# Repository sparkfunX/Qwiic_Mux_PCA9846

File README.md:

SparkFun PCA9846 Qwiic I2C Mux
===========================================================

[*SparkX Qwiic Mux - PCA9846 (SPX-22362)*](https://www.sparkfun.com/products/22362)

Do you have too many sensors with the same I<sup>2</sup>C address? Connect them to the SparkX PCA9846 Qwiic Mux to get them all talking on the same bus! This Qwiic Mux enables communication with multiple I<sup>2</sup>C devices that have the same address. This Qwiic Mux also has eight configurable addresses of its own, allowing for up to 32 I<sup>2</sup>C buses on a single connection. To make it even easier to use this multiplexer, all communication is enacted exclusively via I<sup>2</sup>C, utilizing our handy Qwiic system.

The PCA9846 Qwiic Mux is very similar to our classic [8-channel Qwiic Mux](https://www.sparkfun.com/products/16784), except:

* It has four multiplexed Qwiic ports, plus Qwiic Main In and Out connections, on a super-cute 1" x 1" PCB
* The PCA9846 has a "Who Am I" (Device ID) product identification register which makes it _much_ easier to detect in auto-detect DataLogger / OpenLog applications.

Feel like supporting open source hardware? 
Buy a [board](https://www.sparkfun.com/products/22362) from SparkFun!

Repository Contents
-------------------

* **/Documents** - Datasheet for the PCA9846
* **/Hardware** - Eagle CAD files for the PCB, schematic and dimensions

Arduino Library
--------------

* **[Arduino Library](https://github.com/sparkfun/SparkFun_PCA9846_Mux_Arduino_Library)** - Arduino Library for the PCA9846 I<sup>2</sup>C Mux
* **[Installing an Arduino Library Guide](https://learn.sparkfun.com/tutorials/installing-an-arduino-library)** - Basic information on how to install an Arduino library.

Address Configuration
--------------

The PCA9846 actually supports 16 I<sup>2</sup>C addresses, but to implement all 16 we would have had to include another three solder jumpers.
This is a busy little board, so we decided to only implement 8 configurable addresses.

The PCA9846 appears on two I2C addresses:

* The mux address defined by the A0-A4 jumpers
* Address 0x7C - which is used to read the Device ID

The default mux address is 0x70 (unshifted). You can change it by opening and closing (soldering) the five address jumper pads as follows:

**Jumper Address Selection (Unshifted):**

| Address | A4 | A3 | A2 | A1 | A0 |
|---|---|---|---|---|---|
| 0x70 | Open | Open | Open | Open | **Closed** |
| 0x71 | Open | Open | Open | **Closed** | Open |
| 0x72 | Open | Open | **Closed** | Open | Open |
| 0x73 | Open | **Closed** | Open | Open | Open |
| 0x74 | **Closed** | Open | Open | Open | **Closed** |
| 0x75 | **Closed** | Open | Open | **Closed** | Open |
| 0x76 | **Closed** | Open | **Closed** | Open | Open |
| 0x77 | **Closed** | **Closed** | Open | Open | Open |

License Information
-------------------

This product is _**open source**_! 

Please use, reuse, and modify these files as you see fit. Please maintain attribution to SparkFun Electronics and release anything derivative under the same license.

Distributed as-is; no warranty is given.

- Your friends at SparkFun.

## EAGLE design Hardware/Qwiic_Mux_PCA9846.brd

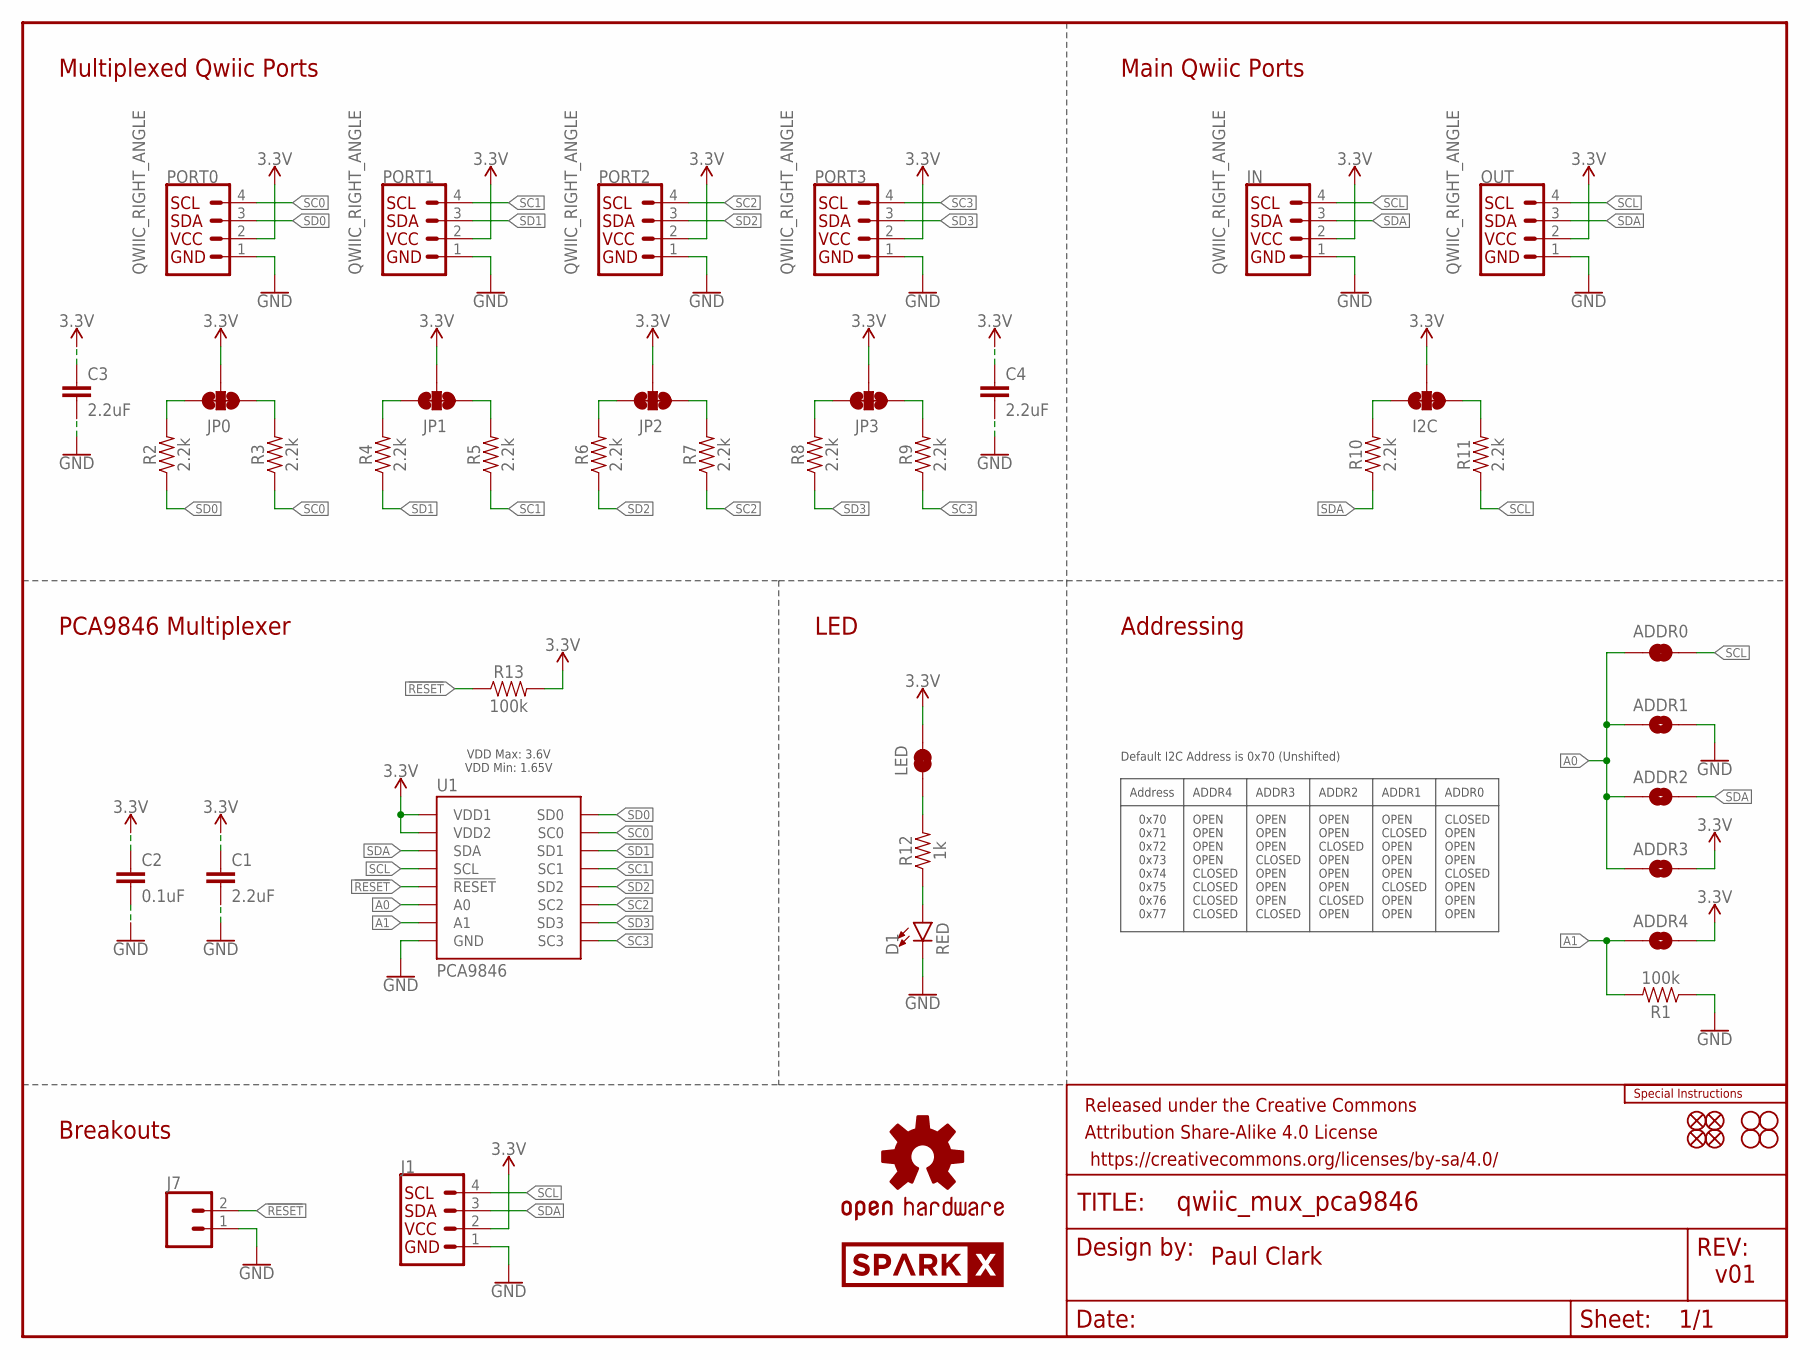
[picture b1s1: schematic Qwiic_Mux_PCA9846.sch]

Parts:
ADDR0: JUMPER-SMT_2_NC_TRACE_SILK; SMT-JUMPER_2_NC_TRACE_SILK
ADDR1, ADDR2, ADDR3, ADDR4: JUMPER-SMT_2_NO_SILK; SMT-JUMPER_2_NO_SILK
C1, C3, C4: 2.2uF; 0402-TIGHT
C2: 0.1uF; 0402-TIGHT
D1: RED; LED-0603
FD1, FD2, FD3, FD4: FIDUCIAL1X2; FIDUCIAL-1X2
FRAME1: FRAME-LETTER; CREATIVE_COMMONS
H1, H2, H3, H4: STAND-OFF
I2C: JUMPER-SMT_3_2-NC_TRACE_SILK; SMT-JUMPER_3_2-NC_TRACE_SILK
IN: QWIIC_RIGHT_ANGLE; JST04_1MM_RA
J1: I2C_STANDARD_NO_SILK; 1X04_NO_SILK
J7: CONN_021X02_NO_SILK; 1X02_NO_SILK
JP0, JP1, JP2, JP3: JUMPER-SMT_3_2-NC_TRACE_SILK; SMT-JUMPER_3_2-NC_TRACE_SILK
LED: JUMPER-SMT_2_NC_TRACE_SILK; SMT-JUMPER_2_NC_TRACE_SILK
LOGO1: SPECIAL_INSTRUCTIONS-ORDERING; ORDERING_INSTRUCTIONS
LOGO4: OSHW-LOGOMINI; OSHW-LOGO-MINI
OUT: QWIIC_RIGHT_ANGLE; JST04_1MM_RA
PORT0, PORT1, PORT2, PORT3: QWIIC_RIGHT_ANGLE; JST04_1MM_RA
R1, R13: 100k; 0402-TIGHT
R2, R3, R4, R5, R6, R7, R8, R9, R10, R11: 2.2k; 0402-TIGHT
R12: 1k; 0402-TIGHT
U1: PCA9846; SOT403-1
U$1: SPARKX-LOGO3; SPARKX-SMALL

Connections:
3.3V: ADDR3.2, ADDR4.2, C1.1, C2.1, C3.1, C4.1, I2C.2, IN.2, J1.2, JP0.2, JP1.2, JP2.2, JP3.2, LED.2, OUT.2, PORT0.2, PORT1.2, PORT2.2, PORT3.2, R13.2, U1.1 (VDD1), U1.16 (VDD2)
!RESET!: J7.2, R13.1, U1.3 (!RESET)
A0: ADDR0.1, ADDR1.1, ADDR2.1, ADDR3.1, U1.2 (A0)
A1: ADDR4.1, R1.2, U1.13 (A1)
GND: ADDR1.2, C1.2, C2.2, C3.2, C4.2, D1.C, IN.1, J1.1, J7.1, OUT.1, PORT0.1, PORT1.1, PORT2.1, PORT3.1, R1.1, U1.8 (GND)
unnamed: JP0.3, R2.2
unnamed: JP0.1, R3.2
unnamed: JP1.3, R4.2
unnamed: JP1.1, R5.2
unnamed: JP2.3, R6.2
unnamed: JP2.1, R7.2
unnamed: JP3.3, R8.2
unnamed: JP3.1, R9.2
unnamed: I2C.3, R10.2
unnamed: I2C.1, R11.2
unnamed: LED.1, R12.2
unnamed: D1.A, R12.1
SC0: PORT0.4, R3.1, U1.5 (SC0)
SC1: PORT1.4, R5.1, U1.7 (SC1)
SC2: PORT2.4, R7.1, U1.10 (SC2)
SC3: PORT3.4, R9.1, U1.12 (SC3)
SCL: ADDR0.2, IN.4, J1.4, OUT.4, R11.1, U1.14 (SCL)
SD0: PORT0.3, R2.1, U1.4 (SD0)
SD1: PORT1.3, R4.1, U1.6 (SD1)
SD2: PORT2.3, R6.1, U1.9 (SD2)
SD3: PORT3.3, R8.1, U1.11 (SD3)
SDA: ADDR2.2, IN.3, J1.3, OUT.3, R10.1, U1.15 (SDA)

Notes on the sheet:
Multiplexed Qwiic Ports
Main Qwiic Ports
PCA9846 Multiplexer
Addressing
Default I2C Address is 0x70 (Unshifted)
Address
ADDR4
ADDR3
ADDR2
ADDR1
ADDR0
0x70 0x71 0x72 0x73 0x74 0x75 0x76 0x77
OPEN OPEN OPEN OPEN CLOSED CLOSED CLOSED CLOSED
OPEN OPEN OPEN CLOSED OPEN OPEN OPEN CLOSED
CLOSED OPEN OPEN OPEN CLOSED OPEN OPEN OPEN
OPEN CLOSED OPEN OPEN OPEN CLOSED OPEN OPEN
OPEN OPEN CLOSED OPEN OPEN OPEN CLOSED OPEN
Paul Clark
v01
Breakouts
LED
VDD Max: 3.6V VDD Min: 1.65V

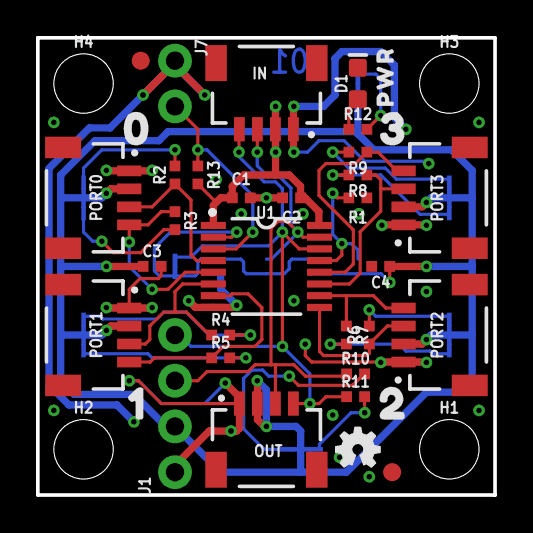
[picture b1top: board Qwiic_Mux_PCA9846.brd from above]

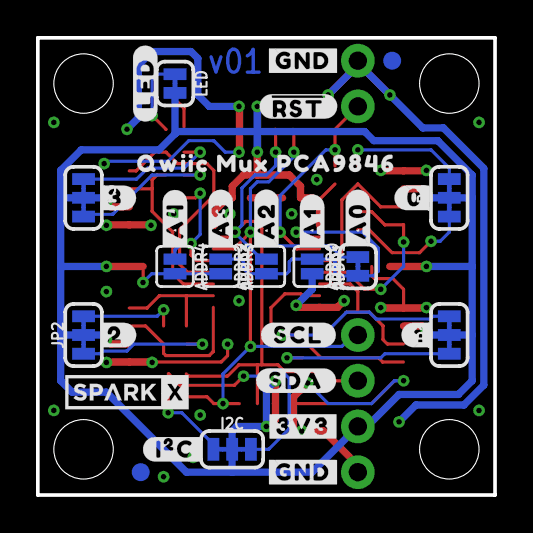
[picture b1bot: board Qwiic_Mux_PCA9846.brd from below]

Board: 2 copper layers, 25.4 x 25.4 mm, 73 parts (32 on the bottom side), 27 nets.

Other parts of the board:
U$2: PWR43214
U$3: 043215
U$4: 10
U$5: 211
U$6: 3212
U$7: ##RST##8
U$8: #0#9
U$9: #1#9
U$10: #2#9
U$11: #3#9
U$12: #3V3#7
U$13: #A0#0
U$14: #A1#1
U$15: #A2#2
U$16: #A3#3
U$17: #A4#4
U$18, U$19: #GND#7
U$21: #SCL#5
U$22: #SDA#6
U$23: #LED#0
U$24: QWIIC_MUX_PCA98461
U$25: #I�C#0

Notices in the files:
parts and their libraries:
SparkFun-Aesthetics: Licensing: Creative Commons ShareAlike 4.0 International - https://creativecommons.org/licenses/by-sa/4.0
SparkFun-Aesthetics: Released under the Creative Commons Attribution Share-Alike 4.0 License
SparkFun-Aesthetics: https://creativecommons.org/licenses/by-sa/4.0
